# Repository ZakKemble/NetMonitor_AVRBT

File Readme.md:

Bluetooth Net Monitor
=====================

http://blog.zakkemble.co.uk/bluetooth-net-monitor-v2/

The firmware .hex files (bootloader & monitor) are compiled for ATmega328P

Fuses for ATmega328/328P  
External full swing crystal 16K CK/14CK + 65ms startup  
Serial program (SPI) enabled  
Brown-out at 2.7V  
Bootloader enabled, 2048 words  
High:		0xD8 (or 0xDF for no bootloader)  
Low:		0xF7  
Extended:	0xFD

--------

`./modem/adsl_btnetmon`  
This is the CGI script which runs on the modem to get ADSL stats (Only tested on Netgear DG834G v3 running OpenWRT)

`./router/btnetmon`  
This is the main program which runs on the router, the binary was compiled on Debain 7.7 x64 so it may or may not work without having to recompile (differently named libs, etc). More info in `./router/Readme.md`

`./utils/lcdBitmapConverter.exe`  
Utility to convert red channel of images (in `./imgs/`) to pixel intensity byte array

`./driver/` contains parts of libusb-win32 available at http://sourceforge.net/apps/trac/libusb-win32/wiki  
`./firmware/` contains the V-USB library available at http://www.obdev.at/products/vusb/index.html  
`./firmware/USBaspLoader/` contains the USBaspLoader bootloader available at https://github.com/baerwolf/USBaspLoader  
Font used is MicroExtendFLF (bold italics) available at http://www.fontspace.com/casady-and-greene/microextendflf  
Third party contents are copyrighted by their respective authors.  
My productions are published under GNU GPL v3 (see License.txt).

--------

Zak Kemble

contact@zakkemble.co.uk

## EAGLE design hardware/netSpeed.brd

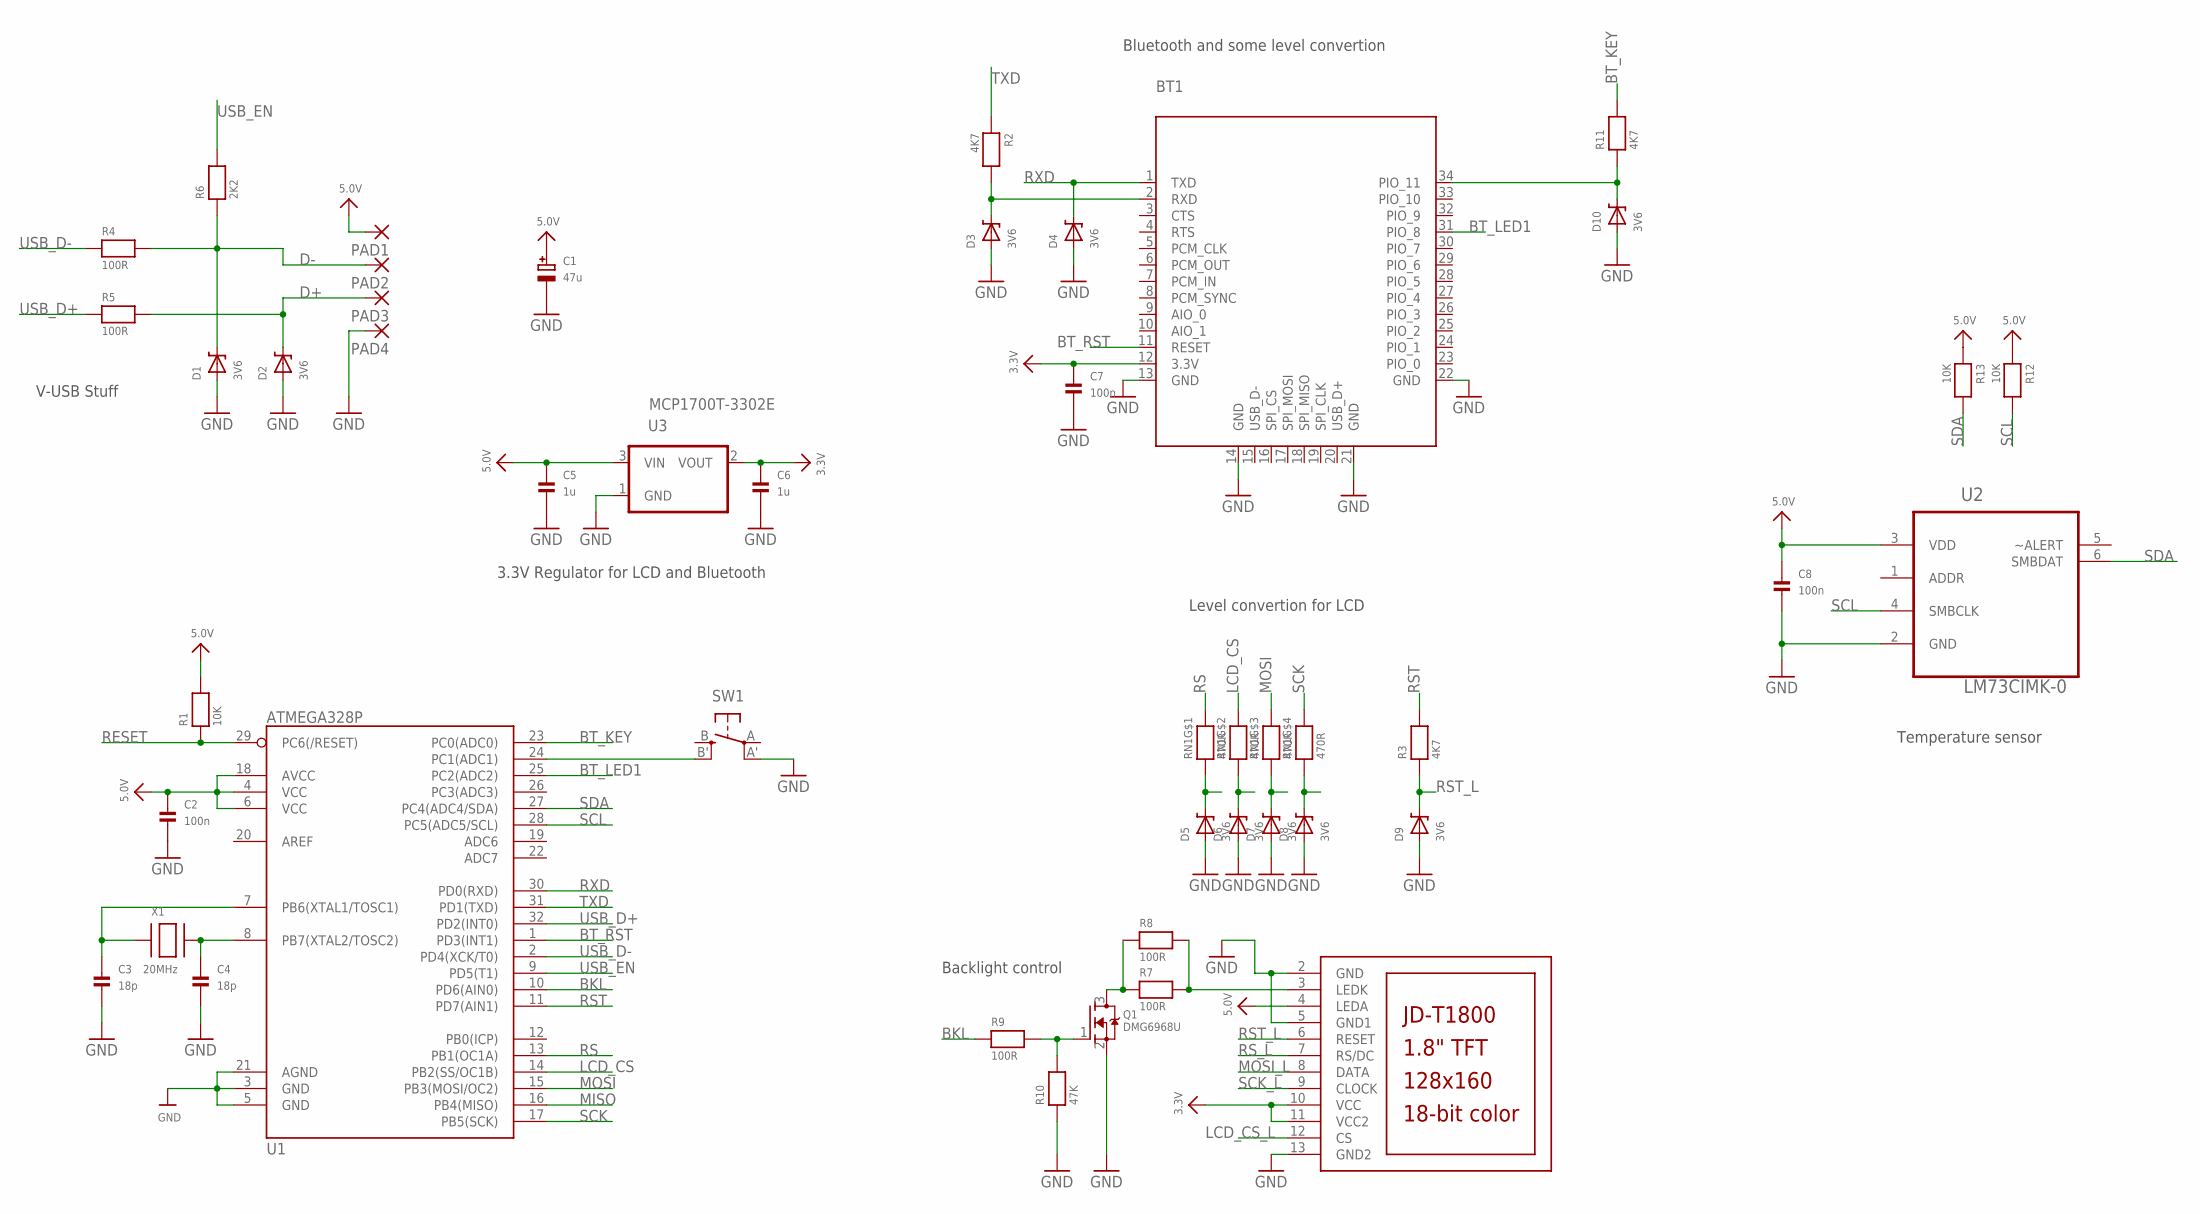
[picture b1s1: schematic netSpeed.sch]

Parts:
BT1: BLUETOOTH_MODULE
C1: 47u; PANASONIC_C
C2, C7, C8: 100n; 0805
C3, C4: 18p; 0805
C5, C6: 1u; 0805
D1, D2, D3, D4, D5, D6, D7, D8, D9, D10: 3V6; SOD-323
LCD1: JD-T1800
PAD1, PAD2, PAD3, PAD4: SMD2; SMD1,27-2,54
Q1: DMG6968U; SOT23-WIDE
R1, R12, R13: 10K; 0805
R2, R3, R11: 4K7; 0805
R4, R5, R7, R8, R9: 100R; 0805
R6: 2K2; 0805
R10: 47K; 0805
RN1: 470R; RESPACK_4X0603
SW1: SPST_TACT; TACT_SMD
U1: ATMEGA328P; TQFP32-08
U2: LM73CIMK-0; SOT95P285X100-6N
U3: MCP1700T-3302E; SOT-23
X1: 20MHz; NX5032

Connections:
3.3V: BT1.12 (3.3V), C6.1, C7.1, LCD1.10 (VCC), LCD1.11 (VCC2), U3.2 (VOUT)
5.0V: C1.+, C2.1, C5.1, C8.1, LCD1.4 (LEDA), PAD1.1, R1.2, R12.1, R13.1, U1.4 (VCC), U1.6 (VCC), U1.18 (AVCC), U2.3 (VDD), U3.3 (VIN)
BKL: R9.1, U1.10 (PD6(AIN0))
BT_KEY: R11.2, U1.23 (PC0(ADC0))
BT_KEY_L: BT1.34 (PIO_11), D10.C, R11.1
BT_LED1: BT1.31 (PIO_8), U1.25 (PC2(ADC2))
BT_RST: BT1.11 (RESET), U1.1 (PD3(INT1))
D+: D2.C, PAD3.1, R5.2
D-: D1.C, PAD2.1, R4.2, R6.1
GND: BT1.13 (GND), BT1.14 (GND), BT1.21 (GND), BT1.22 (GND), C1.-, C2.2, C3.2, C4.2, C5.2, C6.2, C7.2, C8.2, D1.A, D2.A, D3.A, D4.A, D5.A, D6.A, D7.A, D8.A, D9.A, D10.A, LCD1.2 (GND), LCD1.5 (GND1), LCD1.13 (GND2), PAD4.1, Q1.2 (S), R10.1, SW1.A' (P1), U1.3 (GND), U1.5 (GND), U1.21 (AGND), U2.2 (GND), U3.1 (GND)
LCD_CS: RN1.7 (2), U1.14 (PB2(SS/OC1B))
LCD_CS_L: D6.C, LCD1.12 (CS), RN1.2 (1)
MISO: U1.16 (PB4(MISO))
MOSI: RN1.6 (2), U1.15 (PB3(MOSI/OC2))
MOSI_L: D7.C, LCD1.8 (DATA), RN1.3 (1)
unnamed: SW1.B' (S1), U1.24 (PC1(ADC1))
unnamed: C3.1, U1.7 (PB6(XTAL1/TOSC1)), X1.P$1
unnamed: C4.1, U1.8 (PB7(XTAL2/TOSC2)), X1.P$2
unnamed: Q1.1 (G), R9.2, R10.2
unnamed: Q1.3 (D), R7.1, R8.1
unnamed: LCD1.3 (LEDK), R7.2, R8.2
RESET: R1.1, U1.29 (PC6(/RESET))
RS: RN1.8 (2), U1.13 (PB1(OC1A))
RST: R3.2, U1.11 (PD7(AIN1))
RST_L: D9.C, LCD1.6 (RESET), R3.1
RS_L: D5.C, LCD1.7 (RS/DC), RN1.1
RXD: BT1.1 (TXD), D4.C, U1.30 (PD0(RXD))
SCK: RN1.5 (2), U1.17 (PB5(SCK))
SCK_L: D8.C, LCD1.9 (CLOCK), RN1.4 (1)
SCL: R12.2, U1.28 (PC5(ADC5/SCL)), U2.4 (SMBCLK)
SDA: R13.2, U1.27 (PC4(ADC4/SDA)), U2.6 (SMBDAT)
TXD: R2.1, U1.31 (PD1(TXD))
TXD_L: BT1.2 (RXD), D3.C, R2.2
USB_D+: R5.1, U1.32 (PD2(INT0))
USB_D-: R4.1, U1.2 (PD4(XCK/T0))
USB_EN: R6.2, U1.9 (PD5(T1))

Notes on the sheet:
Level convertion for LCD
Temperature sensor
Bluetooth and some level convertion
V-USB Stuff
3.3V Regulator for LCD and Bluetooth
Backlight control

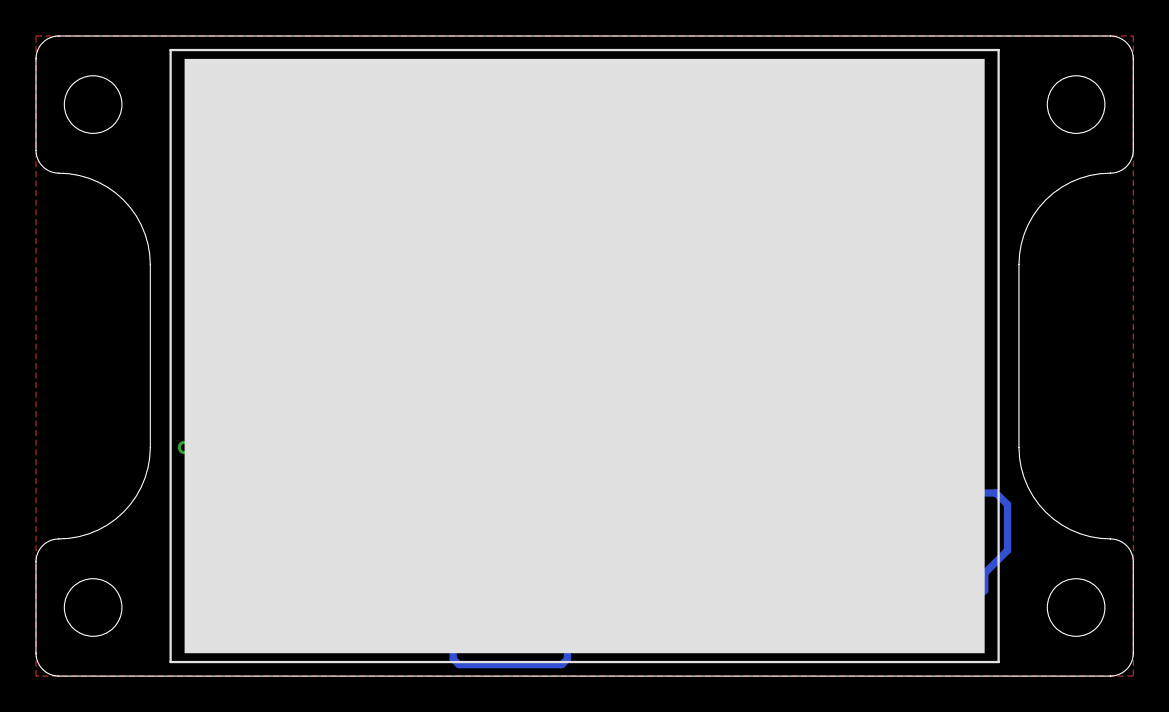
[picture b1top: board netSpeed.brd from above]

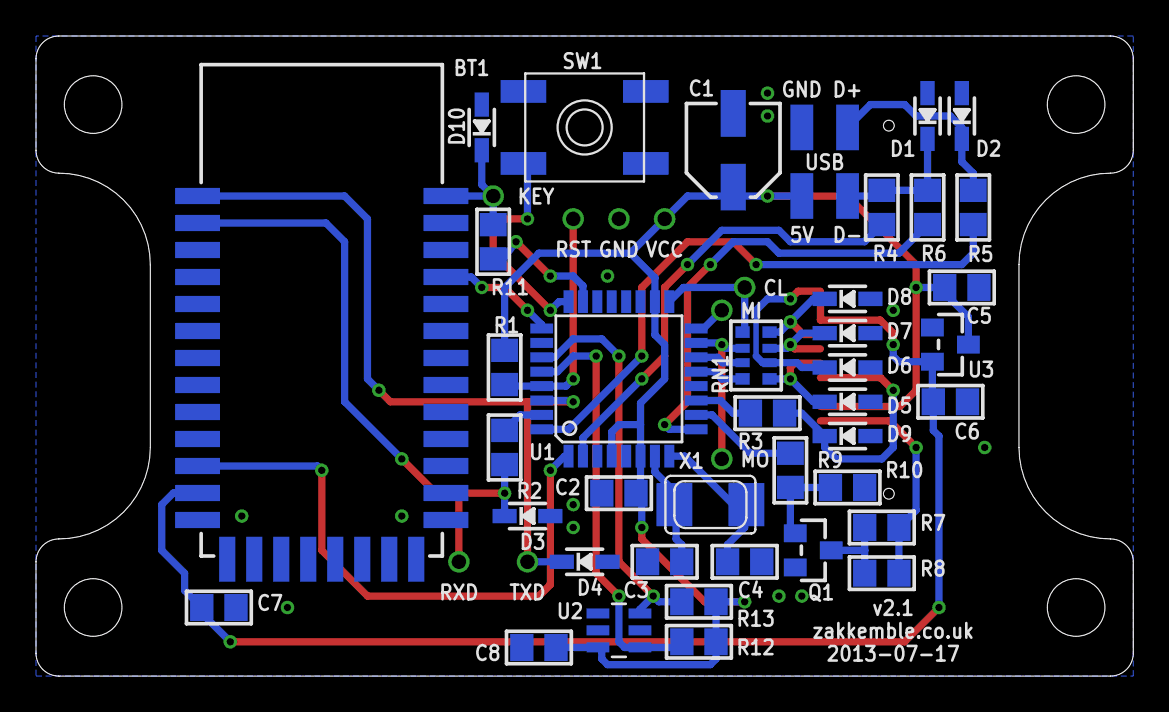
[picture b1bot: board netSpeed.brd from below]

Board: 2 copper layers, 61.0 x 35.6 mm, 44 parts (43 on the bottom side), 35 nets.

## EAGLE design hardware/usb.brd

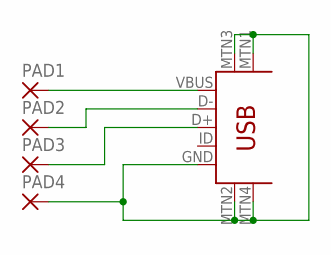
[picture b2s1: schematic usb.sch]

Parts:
PAD1, PAD2, PAD3, PAD4: SMD2; SMD1,27-2,54
USB1: USB-MINIB-5PIN; USB-MINIB

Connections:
GND: PAD4.1, USB1.GND, USB1.MTN1 (MTN2), USB1.MTN2 (MTN3), USB1.MTN3 (MTN1), USB1.MTN4
unnamed: PAD1.1, USB1.VBUS
unnamed: PAD2.1, USB1.D-
unnamed: PAD3.1, USB1.D+

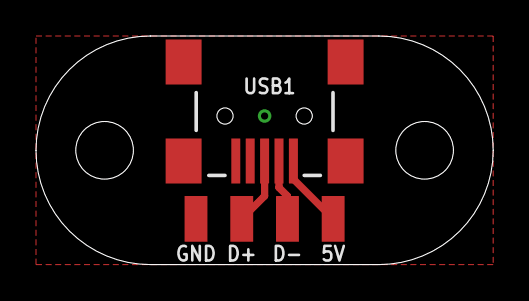
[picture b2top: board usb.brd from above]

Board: 2 copper layers, 25.4 x 12.7 mm, 5 parts (0 on the bottom side), 4 nets.

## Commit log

2014-10-31 :boom::camel: Added .gitattributes & .gitignore files
2014-10-31 Moving stuff to GitHub
2014-10-31 Various updates
    Router program:
    - Support for USB bluetooth adapters (rfcomm)
    - Support for non-point-to-point interfaces
    - Can manually set sync rates
    Net Monitor:
    - Now shows speeds in MBps with 1 decimal place (0.0 - 99.9MBps)

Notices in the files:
parts and their libraries:
SparkFun-DigitalIC: Licensing: CC v3.0 Share-Alike You are welcome to use this library for commercial purposes.
microbuilder: This work is placed in the public domain, and may be freely used for commercial and non-commercial work with the following conditions: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
